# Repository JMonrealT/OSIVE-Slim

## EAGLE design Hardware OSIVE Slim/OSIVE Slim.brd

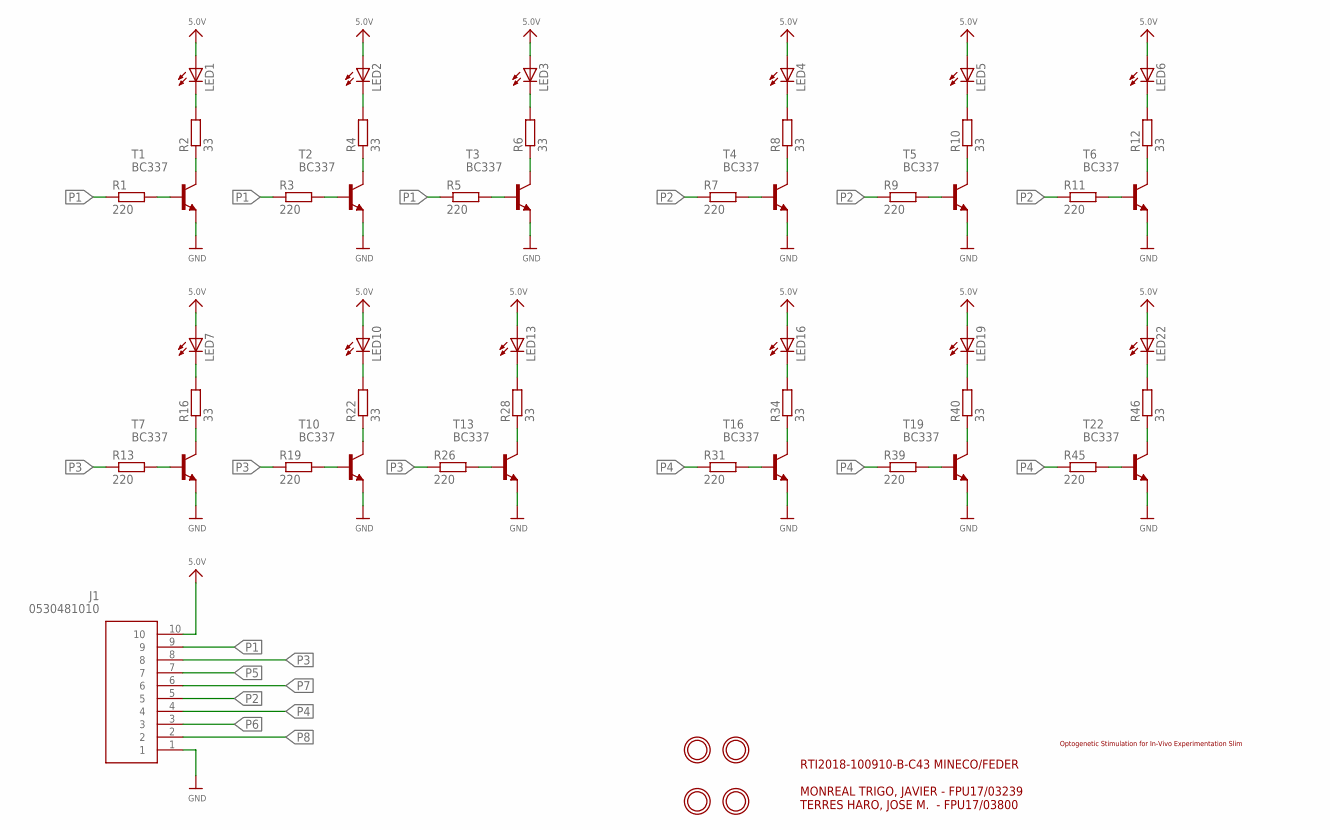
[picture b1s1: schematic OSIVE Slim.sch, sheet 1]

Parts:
H1, H2, H3, H4: MOUNTINGHOLE3.0THIN; MOUNTINGHOLE_3.0_PLATEDTHIN
J1: 0530481010
LED1, LED2, LED3, LED4, LED5, LED6, LED7, LED10, LED13, LED16, LED19, LED22: LED5MM
R1, R3, R5, R7, R9, R11, R13, R19, R26, R31, R39, R45: 220; 0204/7
R2, R4, R6, R8, R10, R12, R16, R22, R28, R34, R40, R46: 33; 0204/7
T1, T2, T3, T4, T5, T6, T7, T10, T13, T16, T19, T22: BC337; TO92

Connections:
5.0V: J1.10, LED1.A, LED2.A, LED3.A, LED4.A, LED5.A, LED6.A, LED7.A, LED10.A, LED13.A, LED16.A, LED19.A, LED22.A; also elsewhere on the board
GND: J1.1, T1.1 (E), T2.1 (E), T3.1 (E), T4.1 (E), T5.1 (E), T6.1 (E), T7.1 (E), T10.1 (E), T13.1 (E), T16.1 (E), T19.1 (E), T22.1 (E); also elsewhere on the board
unnamed: R1.2, T1.2 (B)
unnamed: R3.2, T2.2 (B)
unnamed: R4.1, T2.3 (C)
unnamed: R5.2, T3.2 (B)
unnamed: R2.1, T1.3 (C)
unnamed: R6.1, T3.3 (C)
unnamed: R8.1, T4.3 (C)
unnamed: R10.1, T5.3 (C)
unnamed: R7.2, T4.2 (B)
unnamed: LED1.K (C), R2.2
unnamed: R9.2, T5.2 (B)
unnamed: R12.1, T6.3 (C)
unnamed: R46.1, T22.3 (C)
unnamed: R40.1, T19.3 (C)
unnamed: R34.1, T16.3 (C)
unnamed: R28.1, T13.3 (C)
unnamed: R11.2, T6.2 (B)
unnamed: LED2.K (C), R4.2
unnamed: R13.2, T7.2 (B)
unnamed: R22.1, T10.3 (C)
unnamed: R16.1, T7.3 (C)
unnamed: R19.2, T10.2 (B)
unnamed: LED3.K (C), R6.2
unnamed: R26.2, T13.2 (B)
unnamed: R31.2, T16.2 (B)
unnamed: R39.2, T19.2 (B)
unnamed: R45.2, T22.2 (B)
unnamed: LED4.K (C), R8.2
unnamed: LED5.K (C), R10.2
unnamed: LED6.K (C), R12.2
unnamed: LED7.K (C), R16.2
unnamed: LED10.K (C), R22.2
unnamed: LED13.K (C), R28.2
unnamed: LED16.K (C), R34.2
unnamed: LED19.K (C), R40.2
unnamed: LED22.K (C), R46.2
P1: J1.9, R1.1, R3.1, R5.1
P2: J1.5, R7.1, R9.1, R11.1
P3: J1.8, R13.1, R19.1, R26.1
P4: J1.4, R31.1, R39.1, R45.1
P5: J1.7; also elsewhere on the board
P6: J1.3; also elsewhere on the board
P7: J1.6; also elsewhere on the board
P8: J1.2; also elsewhere on the board

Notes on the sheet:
Optogenetic Stimulation for In-Vivo Experimentation Slim
RTI2018-100910-B-C43 MINECO/FEDER MONREAL TRIGO, JAVIER - FPU17/03239 TERRES HARO, JOSE M. - FPU17/03800

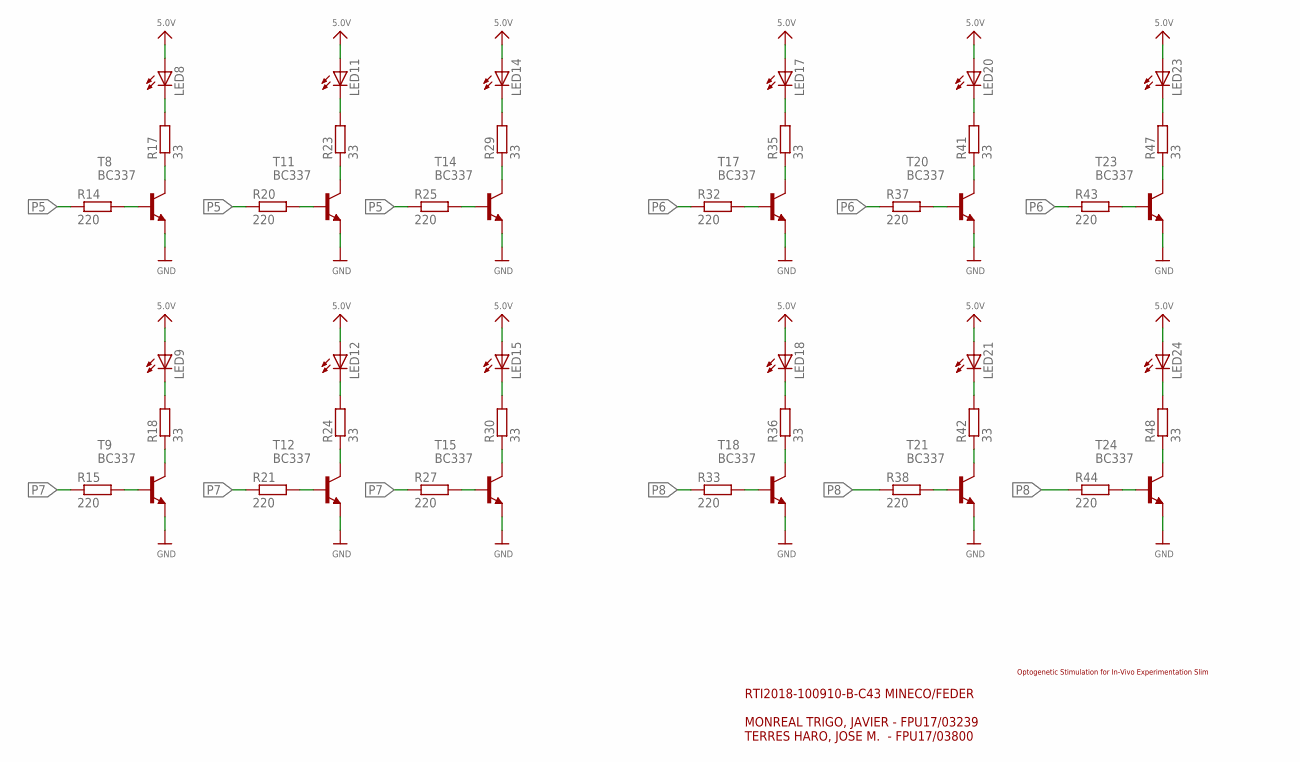
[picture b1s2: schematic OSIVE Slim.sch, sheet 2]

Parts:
LED8, LED9, LED11, LED12, LED14, LED15, LED17, LED18, LED20, LED21, LED23, LED24: LED5MM
R14, R15, R20, R21, R25, R27, R32, R33, R37, R38, R43, R44: 220; 0204/7
R17, R18, R23, R24, R29, R30, R35, R36, R41, R42, R47, R48: 33; 0204/7
T8, T9, T11, T12, T14, T15, T17, T18, T20, T21, T23, T24: BC337; TO92

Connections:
5.0V: LED8.A, LED9.A, LED11.A, LED12.A, LED14.A, LED15.A, LED17.A, LED18.A, LED20.A, LED21.A, LED23.A, LED24.A; also elsewhere on the board
GND: T8.1 (E), T9.1 (E), T11.1 (E), T12.1 (E), T14.1 (E), T15.1 (E), T17.1 (E), T18.1 (E), T20.1 (E), T21.1 (E), T23.1 (E), T24.1 (E); also elsewhere on the board
unnamed: R35.1, T17.3 (C)
unnamed: R29.1, T14.3 (C)
unnamed: R17.1, T8.3 (C)
unnamed: R47.1, T23.3 (C)
unnamed: R41.1, T20.3 (C)
unnamed: R18.1, T9.3 (C)
unnamed: R24.1, T12.3 (C)
unnamed: R30.1, T15.3 (C)
unnamed: R48.1, T24.3 (C)
unnamed: R42.1, T21.3 (C)
unnamed: R36.1, T18.3 (C)
unnamed: R23.1, T11.3 (C)
unnamed: R43.2, T23.2 (B)
unnamed: R37.2, T20.2 (B)
unnamed: R32.2, T17.2 (B)
unnamed: R25.2, T14.2 (B)
unnamed: R20.2, T11.2 (B)
unnamed: R14.2, T8.2 (B)
unnamed: R15.2, T9.2 (B)
unnamed: R21.2, T12.2 (B)
unnamed: R27.2, T15.2 (B)
unnamed: R33.2, T18.2 (B)
unnamed: R38.2, T21.2 (B)
unnamed: R44.2, T24.2 (B)
unnamed: LED8.K (C), R17.2
unnamed: LED11.K (C), R23.2
unnamed: LED14.K (C), R29.2
unnamed: LED17.K (C), R35.2
unnamed: LED20.K (C), R41.2
unnamed: LED23.K (C), R47.2
unnamed: LED9.K (C), R18.2
unnamed: LED12.K (C), R24.2
unnamed: LED15.K (C), R30.2
unnamed: LED18.K (C), R36.2
unnamed: LED21.K (C), R42.2
unnamed: LED24.K (C), R48.2
P5: R14.1, R20.1, R25.1; also elsewhere on the board
P6: R32.1, R37.1, R43.1; also elsewhere on the board
P7: R15.1, R21.1, R27.1; also elsewhere on the board
P8: R33.1, R38.1, R44.1; also elsewhere on the board

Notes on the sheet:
Optogenetic Stimulation for In-Vivo Experimentation Slim
RTI2018-100910-B-C43 MINECO/FEDER MONREAL TRIGO, JAVIER - FPU17/03239 TERRES HARO, JOSE M. - FPU17/03800

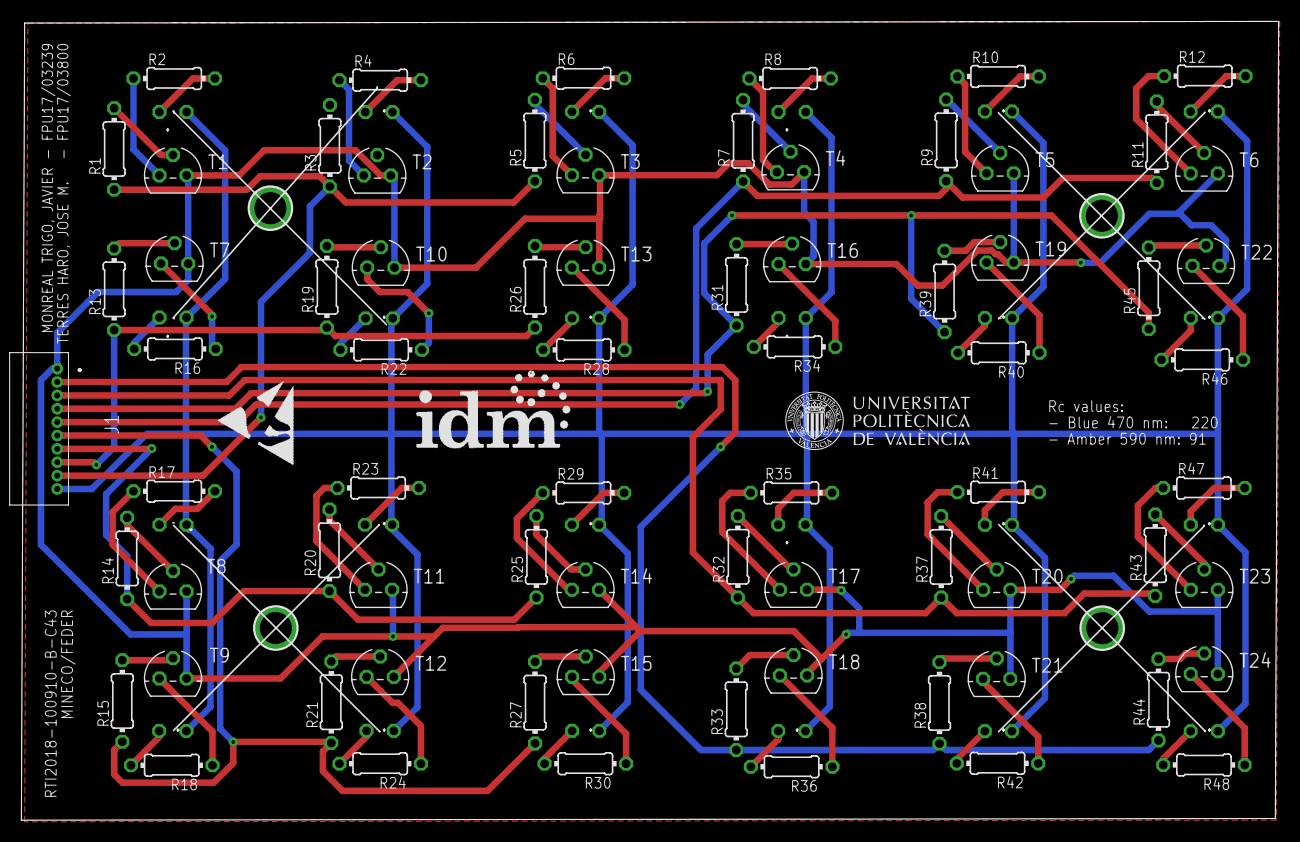
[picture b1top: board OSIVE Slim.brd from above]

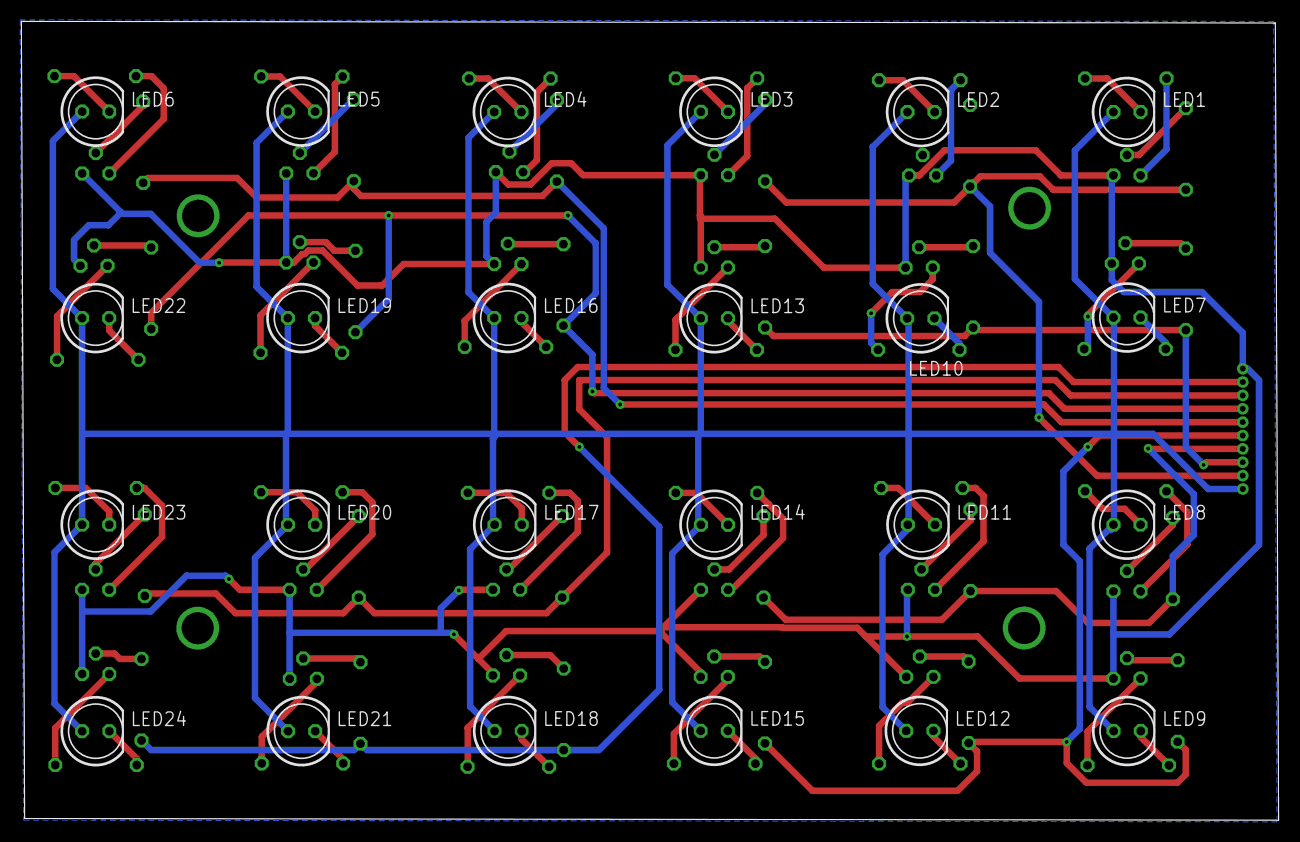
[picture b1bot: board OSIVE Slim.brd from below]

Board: 2 copper layers, 117.5 x 74.7 mm, 101 parts (24 on the bottom side), 82 nets.

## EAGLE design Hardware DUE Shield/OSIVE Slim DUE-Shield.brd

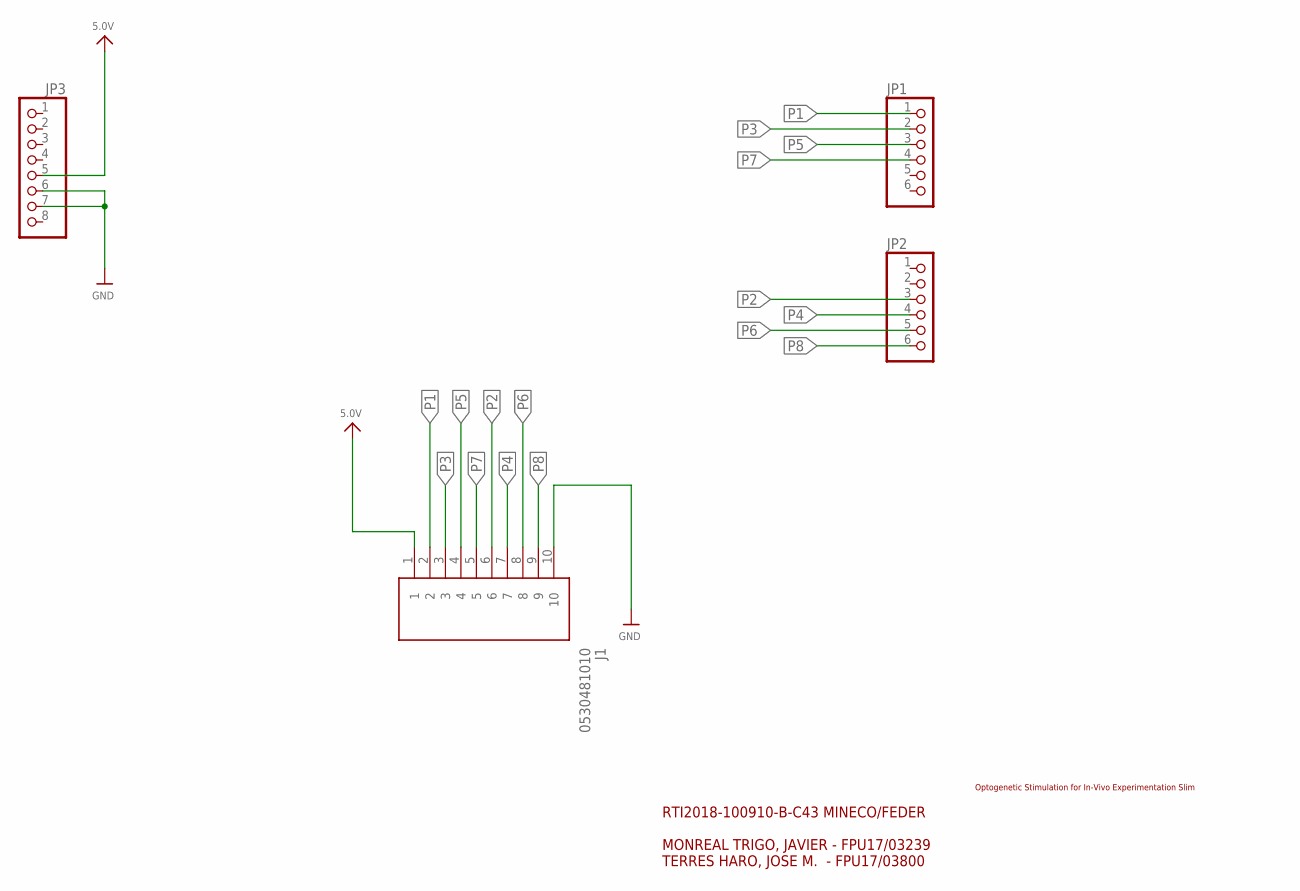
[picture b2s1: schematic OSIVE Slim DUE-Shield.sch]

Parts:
J1: 0530481010
JP1, JP2: HEADER-1X6; 1X06_OVAL
JP3: HEADER-1X8; 1X08_OVAL

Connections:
5.0V: J1.1, JP3.5
GND: J1.10, JP3.6, JP3.7
P1: J1.2, JP1.1
P2: J1.6, JP2.3
P3: J1.3, JP1.2
P4: J1.7, JP2.4
P5: J1.4, JP1.3
P6: J1.8, JP2.5
P7: J1.5, JP1.4
P8: J1.9, JP2.6

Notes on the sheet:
Optogenetic Stimulation for In-Vivo Experimentation Slim
RTI2018-100910-B-C43 MINECO/FEDER MONREAL TRIGO, JAVIER - FPU17/03239 TERRES HARO, JOSE M. - FPU17/03800

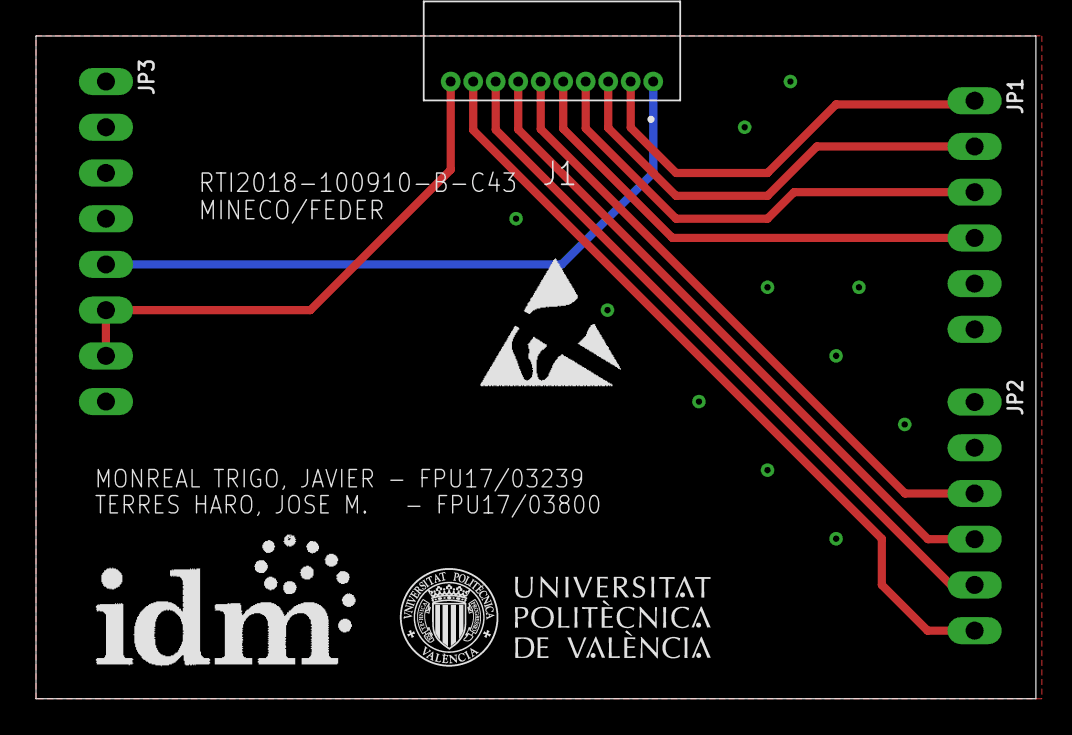
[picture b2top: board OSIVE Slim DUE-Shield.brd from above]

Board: 2 copper layers, 55.5 x 36.8 mm, 4 parts (0 on the bottom side), 10 nets.

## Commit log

2023-02-21 CC BY-NC-SA LICENSE
    CC BY-NC-SA
    This license allows reusers to distribute, remix, adapt, and build upon the material in any medium or format for noncommercial purposes only, and only so long as attribution is given to the creator. 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
    For commercial permissions contact: jmonreal@upv.es

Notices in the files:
parts and their libraries:
microbuilder: This work is placed in the public domain, and may be freely used for commercial and non-commercial work with the following conditions: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
